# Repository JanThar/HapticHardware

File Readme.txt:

Different (hardware) methods to drive large arrays of vibration motors.

1) I2C

Roughly based upon the Adafruit 16* Servo board with the PCA9685, includes driver for 16 vibration motors and an adjustable voltage regulator for the motors and the driver. Easiest way to solder (and cheapest), easy to use, and up to 62 boards in a row thanks to six dress pins (solder different resistors)

2) Serial

Misuse of the WS2811 LED driver, you can also drive up to 3 vibration motors with on chip (instead of the three colors), in this case we use just one for a vibration motor and the other two for control less. As a result, up to 1024 of these boards can be daisy chained, using the same programs and library as for the led strips. Main disadvantage for a wearable use case is that if one of these breaks, the rest behind will be dead as well. Therefore use only for static devices.

3) Parallel

A dedicated micro controller (in this case: A MSP430G2553 (small package and two wire programming interface)) drives up to four vibration motors. Wiring is done with a standard 4 wire flat ribbon cable with crimped connectors. A voltage regulator board in certain distances (corresponding to power consumption - see max current for flat ribbon cables) will regulate voltage down from a higher supply voltage. While wiring is easy, you have to program each controller with a unique ID (all boards receive serial commands parallel) - the programing interface is also included in the 4 wire connector.

Can be found in the deprecated files, at the moment we use the I2C version, with 3D-design files for holder for 
- Intel Realsense Camera
- Up Bord (Chassis from https://sketchfab.com/models/c38cb411538d41c281d08b0f8ed3b875)
- Battery Pack  (Sandberg PowerBank 18200)
- Wires, PCBs
- Motor (5mm diameter, 8mm length, integrated excenter). Since one should use easily available motors, also motors with external excenter can be used, for this case we added a univeral usable, and size-customizable for this motors as holder, alternative the flatter package can be adjusted. The motor diamter should be bigger than the excenter, and for the latter housing the motor diameter should be around 5mm, to use drinking straws as protection cover. Otherwise, the motor should work with 3.3V and should have longer sopper spring pads for easier soldering and reliable connection

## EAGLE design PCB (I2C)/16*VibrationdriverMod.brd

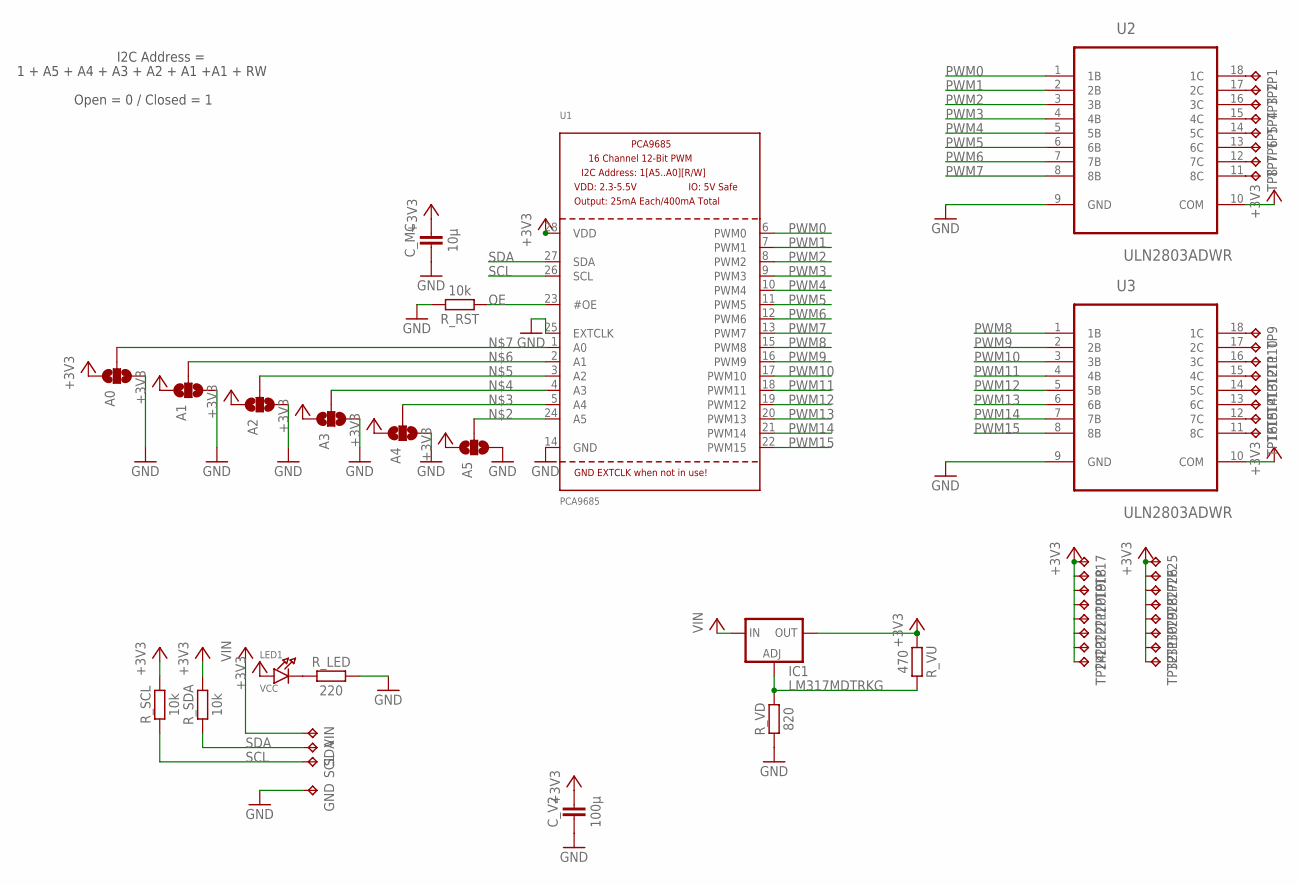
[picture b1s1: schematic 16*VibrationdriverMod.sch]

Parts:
A0, A1, A2, A3, A4, A5: SOLDERJUMPER_2WAYPASTE2&3; SJ_3_PASTE2&3
C_MC: 10µ; 603
C_V2: 100µ; 1206
GND: TPTP16SQ; TP16SQ
IC1: LM317MDTRKG; DPACK
LED1: VCC; CHIPLED_0603
R_LED: 220; 603
R_RST: 10k; 603
R_SCL: 10k; 603
R_SDA: 10k; 603
R_VD: 820; 603
R_VU: 470; 603
SCL: TPTP16SQ; TP16SQ
SDA: TPTP16SQ; TP16SQ
TP1, TP2, TP3, TP4, TP5, TP6, TP7, TP8, TP9, TP10, TP11, TP12, TP13, TP14, TP15, TP16, TP17, TP18, TP19, TP20, TP21, TP22, TP23, TP24, TP25, TP26, TP27, TP28, TP29, TP30, TP31, TP32: TPTP16SQ; TP16SQ
U1: PCA9685; TSSOP28
U2, U3: ULN2803ADWR; SOIC127P1030X265-18N
VIN: TPTP16SQ; TP16SQ

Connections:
+3V3: A0.1, A1.1, A2.1, A3.1, A4.1, A5.1, C_MC.2, C_V2.2, IC1.4 (OUT), LED1.A, R_SCL.2, R_SDA.2, R_VU.1, TP17.TP, TP18.TP, TP19.TP, TP20.TP, TP21.TP, TP22.TP, TP23.TP, TP24.TP, TP25.TP, TP26.TP, TP27.TP, TP28.TP, TP29.TP, TP30.TP, TP31.TP, TP32.TP, U1.28 (VDD), U2.10 (COM), U3.10 (COM)
GND: A0.3, A1.3, A2.3, A3.3, A4.3, A5.3, C_MC.1, C_V2.1, GND.TP, R_LED.2, R_RST.2, R_VD.1, U1.14 (GND), U1.25 (EXTCLK), U2.9 (GND), U3.9 (GND)
unnamed: LED1.C, R_LED.1
unnamed: A5.2, U1.24 (A5)
unnamed: A4.2, U1.5 (A4)
unnamed: A3.2, U1.4 (A3)
unnamed: A2.2, U1.3 (A2)
unnamed: A1.2, U1.2 (A1)
unnamed: A0.2, U1.1 (A0)
unnamed: TP1.TP, U2.18 (1C)
unnamed: IC1.1 (ADJ), R_VD.2, R_VU.2
unnamed: TP2.TP, U2.17 (2C)
unnamed: TP3.TP, U2.16 (3C)
unnamed: TP4.TP, U2.15 (4C)
unnamed: TP5.TP, U2.14 (5C)
unnamed: TP6.TP, U2.13 (6C)
unnamed: TP7.TP, U2.12 (7C)
unnamed: TP8.TP, U2.11 (8C)
unnamed: TP9.TP, U3.18 (1C)
unnamed: TP10.TP, U3.17 (2C)
unnamed: TP11.TP, U3.16 (3C)
unnamed: TP12.TP, U3.15 (4C)
unnamed: TP13.TP, U3.14 (5C)
unnamed: TP14.TP, U3.13 (6C)
unnamed: TP15.TP, U3.12 (7C)
unnamed: TP16.TP, U3.11 (8C)
OE: R_RST.1, U1.23 (#OE)
PWM0: U1.6 (PWM0), U2.1 (1B)
PWM1: U1.7 (PWM1), U2.2 (2B)
PWM2: U1.8 (PWM2), U2.3 (3B)
PWM3: U1.9 (PWM3), U2.4 (4B)
PWM4: U1.10 (PWM4), U2.5 (5B)
PWM5: U1.11 (PWM5), U2.6 (6B)
PWM6: U1.12 (PWM6), U2.7 (7B)
PWM7: U1.13 (PWM7), U2.8 (8B)
PWM8: U1.15 (PWM8), U3.1 (1B)
PWM9: U1.16 (PWM9), U3.2 (2B)
PWM10: U1.17 (PWM10), U3.3 (3B)
PWM11: U1.18 (PWM11), U3.4 (4B)
PWM12: U1.19 (PWM12), U3.5 (5B)
PWM13: U1.20 (PWM13), U3.6 (6B)
PWM14: U1.21 (PWM14), U3.7 (7B)
PWM15: U1.22 (PWM15), U3.8 (8B)
SCL: R_SCL.1, SCL.TP, U1.26 (SCL)
SDA: R_SDA.1, SDA.TP, U1.27 (SDA)
VCC: IC1.3 (IN), VIN.TP

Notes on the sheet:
1 + A5 + A4 + A3 + A2 + A1 +A1 + RW
I2C Address =
Open = 0 / Closed = 1

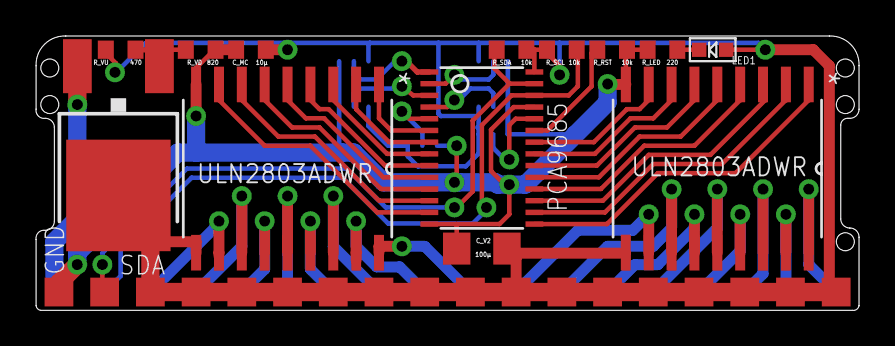
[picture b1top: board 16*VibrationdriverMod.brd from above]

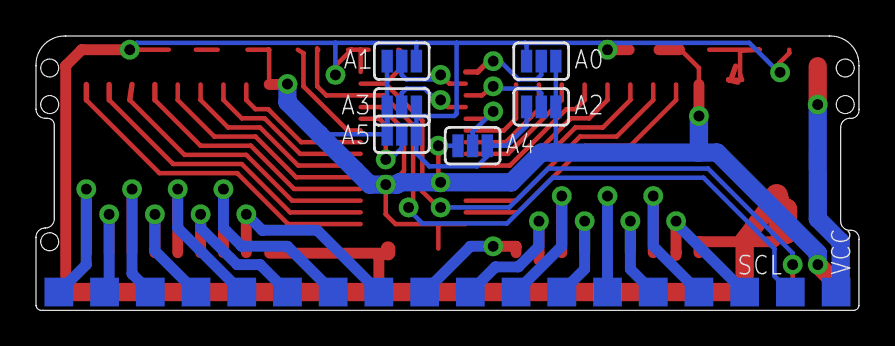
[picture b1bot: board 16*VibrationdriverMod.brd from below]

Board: 2 copper layers, 45.7 x 15.2 mm, 55 parts (24 on the bottom side), 46 nets.

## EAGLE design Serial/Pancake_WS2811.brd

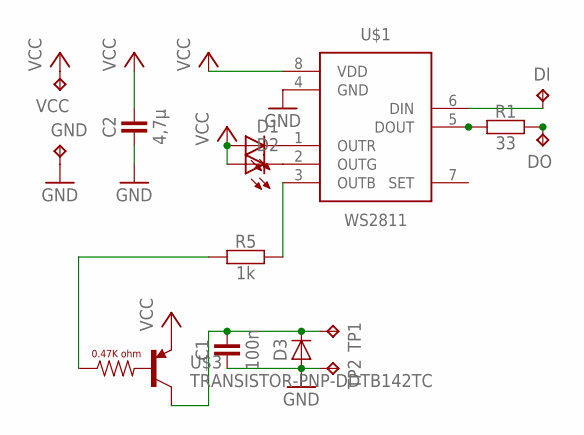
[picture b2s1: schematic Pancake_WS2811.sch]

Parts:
C1: 100n; C0603
C2: 4,7µ; C0603
D1, D2: LED-0603; C0603
D3: DIODE-SOD110; SOD110
DI: TPTP08SQ; TP08SQ
DO: TPTP08SQ; TP08SQ
GND: TPTP08SQ; TP08SQ
R1: 33; C0603
R5: 1k; C0603
TP1, TP2: TPTP20R; TP20R
U$1: WS2811; SOP-8
U$3: TRANSISTOR-PNP-DDTB142TC; SOT23-3
VCC: TPTP08SQ; TP08SQ

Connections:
DIN: DI.TP, U$1.6 (DIN)
GND: C1.1, C2.1, D3.A, GND.TP, TP2.TP, U$1.4 (GND)
unnamed: C1.2, D3.C, TP1.TP, U$3.3 (C)
unnamed: R1.1, U$1.5 (DOUT)
unnamed: DO.TP, R1.2
unnamed: D1.C, U$1.1 (OUTR)
unnamed: D2.C, U$1.2 (OUTG)
unnamed: R5.1, U$3.1 (B)
unnamed: R5.2, U$1.3 (OUTB)
VCC: C2.2, D1.A, D2.A, U$1.8 (VDD), U$3.2 (E), VCC.TP

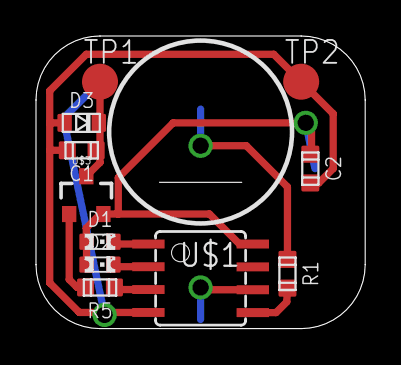
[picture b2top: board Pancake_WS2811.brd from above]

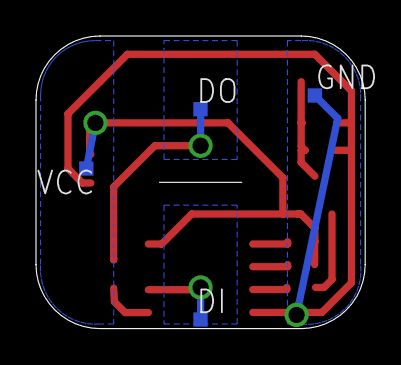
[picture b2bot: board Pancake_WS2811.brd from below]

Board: 2 copper layers, 18.3 x 16.3 mm, 15 parts (4 on the bottom side), 10 nets.

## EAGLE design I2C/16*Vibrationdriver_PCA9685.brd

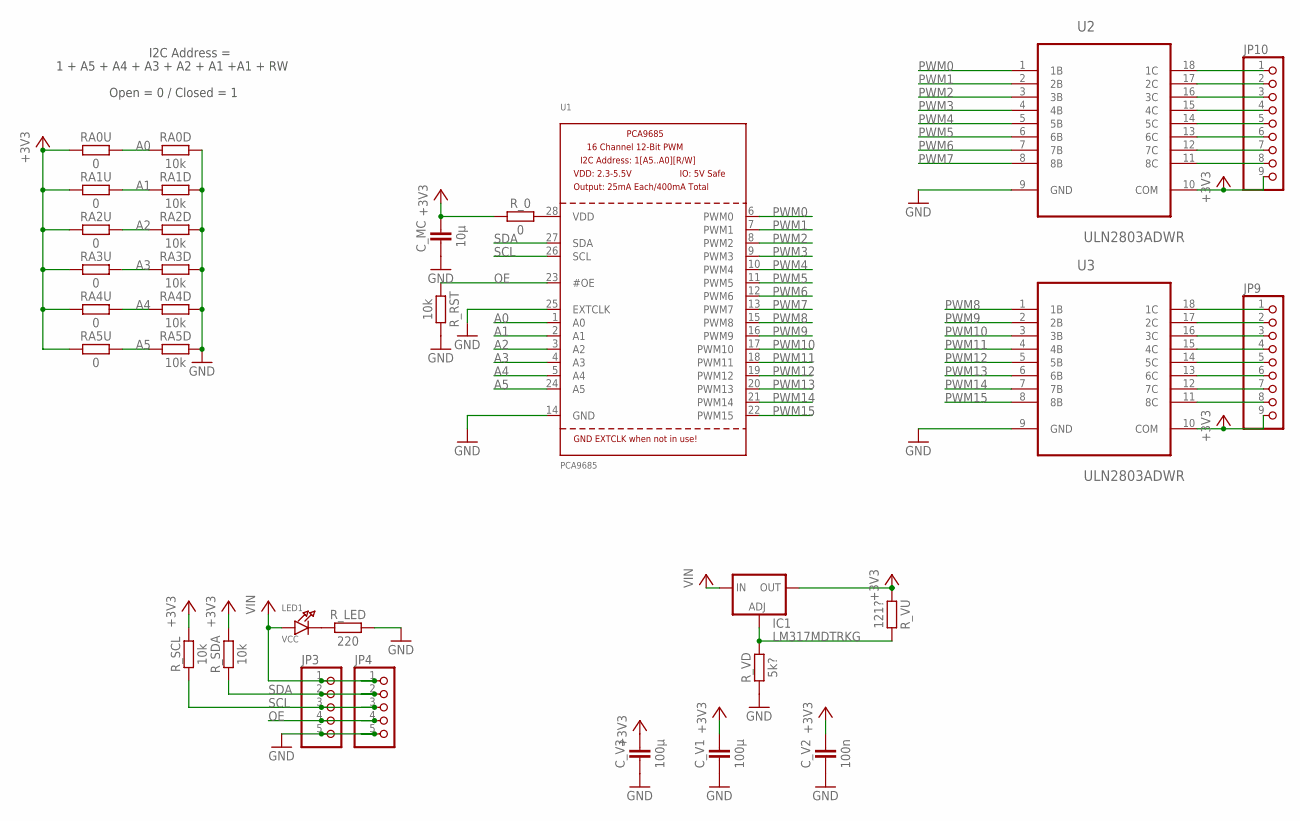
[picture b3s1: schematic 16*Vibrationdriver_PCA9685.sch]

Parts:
C_MC: 10µ; 603
C_V1, C_V3: 100µ; 1206
C_V2: 100n; 603
IC1: LM317MDTRKG; DPACK
JP3, JP4: PINHD-1X5; 1X05
JP9, JP10: PINHD-1X9; 1X09
LED1: VCC; CHIPLED_0805
RA0D, RA1D, RA2D, RA3D, RA4D, RA5D: 10k; 603
RA0U, RA1U, RA2U, RA3U, RA4U, RA5U: 0; 603
R_0: 0; 603
R_LED: 220; 603
R_RST: 10k; 603
R_SCL: 10k; 603
R_SDA: 10k; 603
R_VD: 5k?; 603
R_VU: 121?; 603
U1: PCA9685; TSSOP28
U2, U3: ULN2803ADWR; SOIC127P1030X265-18N

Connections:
+3V3: C_MC.2, C_V1.2, C_V2.2, C_V3.2, IC1.4 (OUT), JP9.9, JP10.9, RA0U.1, RA1U.1, RA2U.1, RA3U.1, RA4U.1, RA5U.1, R_0.1, R_SCL.2, R_SDA.2, R_VU.1, U2.10 (COM), U3.10 (COM)
A0: RA0D.1, RA0U.2, U1.1 (A0)
A1: RA1D.1, RA1U.2, U1.2 (A1)
A2: RA2D.1, RA2U.2, U1.3 (A2)
A3: RA3D.1, RA3U.2, U1.4 (A3)
A4: RA4D.1, RA4U.2, U1.5 (A4)
A5: RA5D.1, RA5U.2, U1.24 (A5)
GND: C_MC.1, C_V1.1, C_V2.1, C_V3.1, JP3.5, JP4.5, RA0D.2, RA1D.2, RA2D.2, RA3D.2, RA4D.2, RA5D.2, R_LED.2, R_RST.2, R_VD.1, U1.14 (GND), U1.25 (EXTCLK), U2.9 (GND), U3.9 (GND)
unnamed: LED1.C, R_LED.1
unnamed: R_0.2, U1.28 (VDD)
unnamed: JP10.1, U2.18 (1C)
unnamed: IC1.1 (ADJ), R_VD.2, R_VU.2
unnamed: JP10.2, U2.17 (2C)
unnamed: JP10.3, U2.16 (3C)
unnamed: JP10.4, U2.15 (4C)
unnamed: JP10.5, U2.14 (5C)
unnamed: JP10.6, U2.13 (6C)
unnamed: JP10.7, U2.12 (7C)
unnamed: JP10.8, U2.11 (8C)
unnamed: JP9.1, U3.18 (1C)
unnamed: JP9.2, U3.17 (2C)
unnamed: JP9.3, U3.16 (3C)
unnamed: JP9.4, U3.15 (4C)
unnamed: JP9.5, U3.14 (5C)
unnamed: JP9.6, U3.13 (6C)
unnamed: JP9.7, U3.12 (7C)
unnamed: JP9.8, U3.11 (8C)
OE: JP3.4, JP4.4, R_RST.1, U1.23 (#OE)
PWM0: U1.6 (PWM0), U2.1 (1B)
PWM1: U1.7 (PWM1), U2.2 (2B)
PWM2: U1.8 (PWM2), U2.3 (3B)
PWM3: U1.9 (PWM3), U2.4 (4B)
PWM4: U1.10 (PWM4), U2.5 (5B)
PWM5: U1.11 (PWM5), U2.6 (6B)
PWM6: U1.12 (PWM6), U2.7 (7B)
PWM7: U1.13 (PWM7), U2.8 (8B)
PWM8: U1.15 (PWM8), U3.1 (1B)
PWM9: U1.16 (PWM9), U3.2 (2B)
PWM10: U1.17 (PWM10), U3.3 (3B)
PWM11: U1.18 (PWM11), U3.4 (4B)
PWM12: U1.19 (PWM12), U3.5 (5B)
PWM13: U1.20 (PWM13), U3.6 (6B)
PWM14: U1.21 (PWM14), U3.7 (7B)
PWM15: U1.22 (PWM15), U3.8 (8B)
SCL: JP3.3, JP4.3, R_SCL.1, U1.26 (SCL)
SDA: JP3.2, JP4.2, R_SDA.1, U1.27 (SDA)
VCC: IC1.3 (IN), JP3.1, JP4.1, LED1.A

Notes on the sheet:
1 + A5 + A4 + A3 + A2 + A1 +A1 + RW
I2C Address =
Open = 0 / Closed = 1

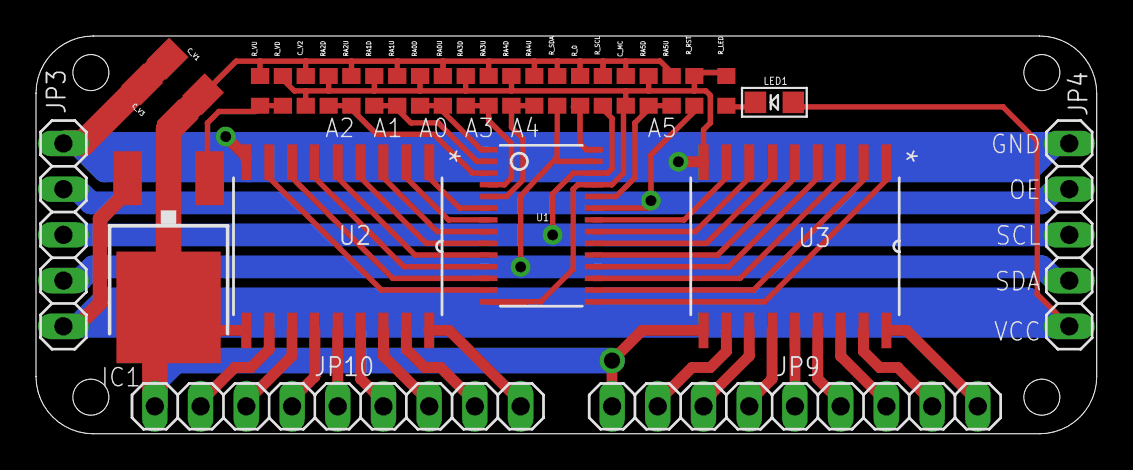
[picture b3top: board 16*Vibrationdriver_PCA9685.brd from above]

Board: 2 copper layers, 58.9 x 22.1 mm, 32 parts (0 on the bottom side), 47 nets.

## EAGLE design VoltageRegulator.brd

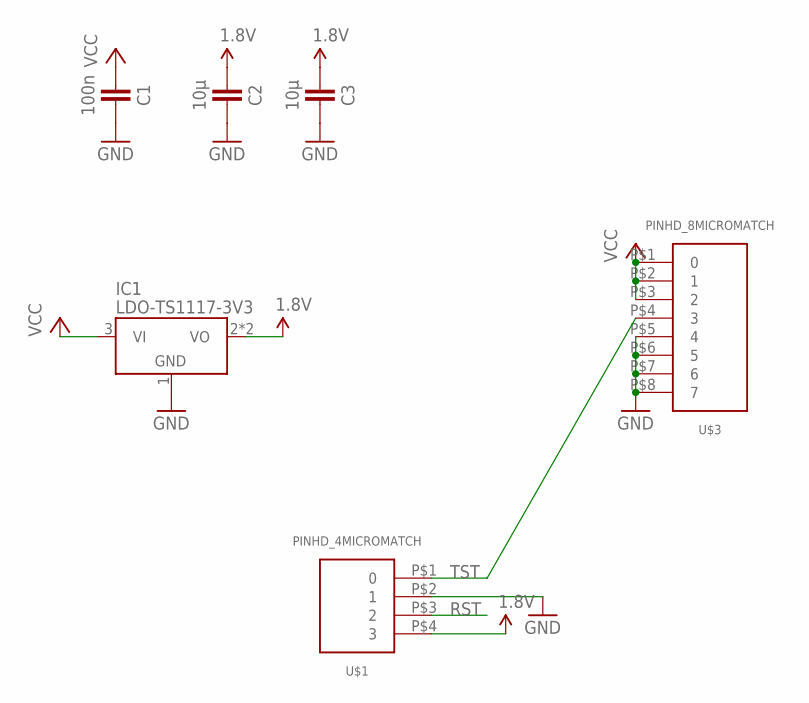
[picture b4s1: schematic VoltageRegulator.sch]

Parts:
C1: 100n; 1206
C2, C3: 10µ; 1206
IC1: LDO-TS1117-3V3; SOT223
U$1: PINHD_4MICROMATCH; MICROMATCH4P0L
U$3: PINHD_8MICROMATCH; MICROMATCH8POL

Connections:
1.8V: C2.1, C3.1, IC1.2 (VO), IC1.4 (VO), U$1.P$4 (3)
GND: C1.2, C2.2, C3.2, IC1.1 (GND), U$1.P$2 (1), U$3.P$5 (4), U$3.P$6 (5), U$3.P$7 (6), U$3.P$8 (7)
RST: U$1.P$3 (2)
TST: U$1.P$1 (0), U$3.P$4 (3)
VCC: C1.1, IC1.3 (VI), U$3.P$1 (0), U$3.P$2 (1), U$3.P$3 (2)

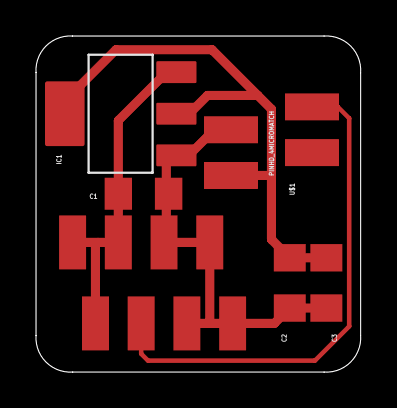
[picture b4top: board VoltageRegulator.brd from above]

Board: 2 copper layers, 18.0 x 18.7 mm, 6 parts (0 on the bottom side), 4 nets.

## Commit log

2016-08-30 Inititial Commit
2016-08-30 cleanup, read me
2016-08-30 wrong cable
2016-08-30 Add example images
2016-08-31 Update pictures, pancake
2016-10-31 Upload image
2017-04-23 clean up
2017-04-23 Textile
2019-06-07 games

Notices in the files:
parts and their libraries:
SparkFun-Retired: Licensing:Creative Commons ShareAlike 4.0 International - https://creativecommons.org/licenses/by-sa/4.0
